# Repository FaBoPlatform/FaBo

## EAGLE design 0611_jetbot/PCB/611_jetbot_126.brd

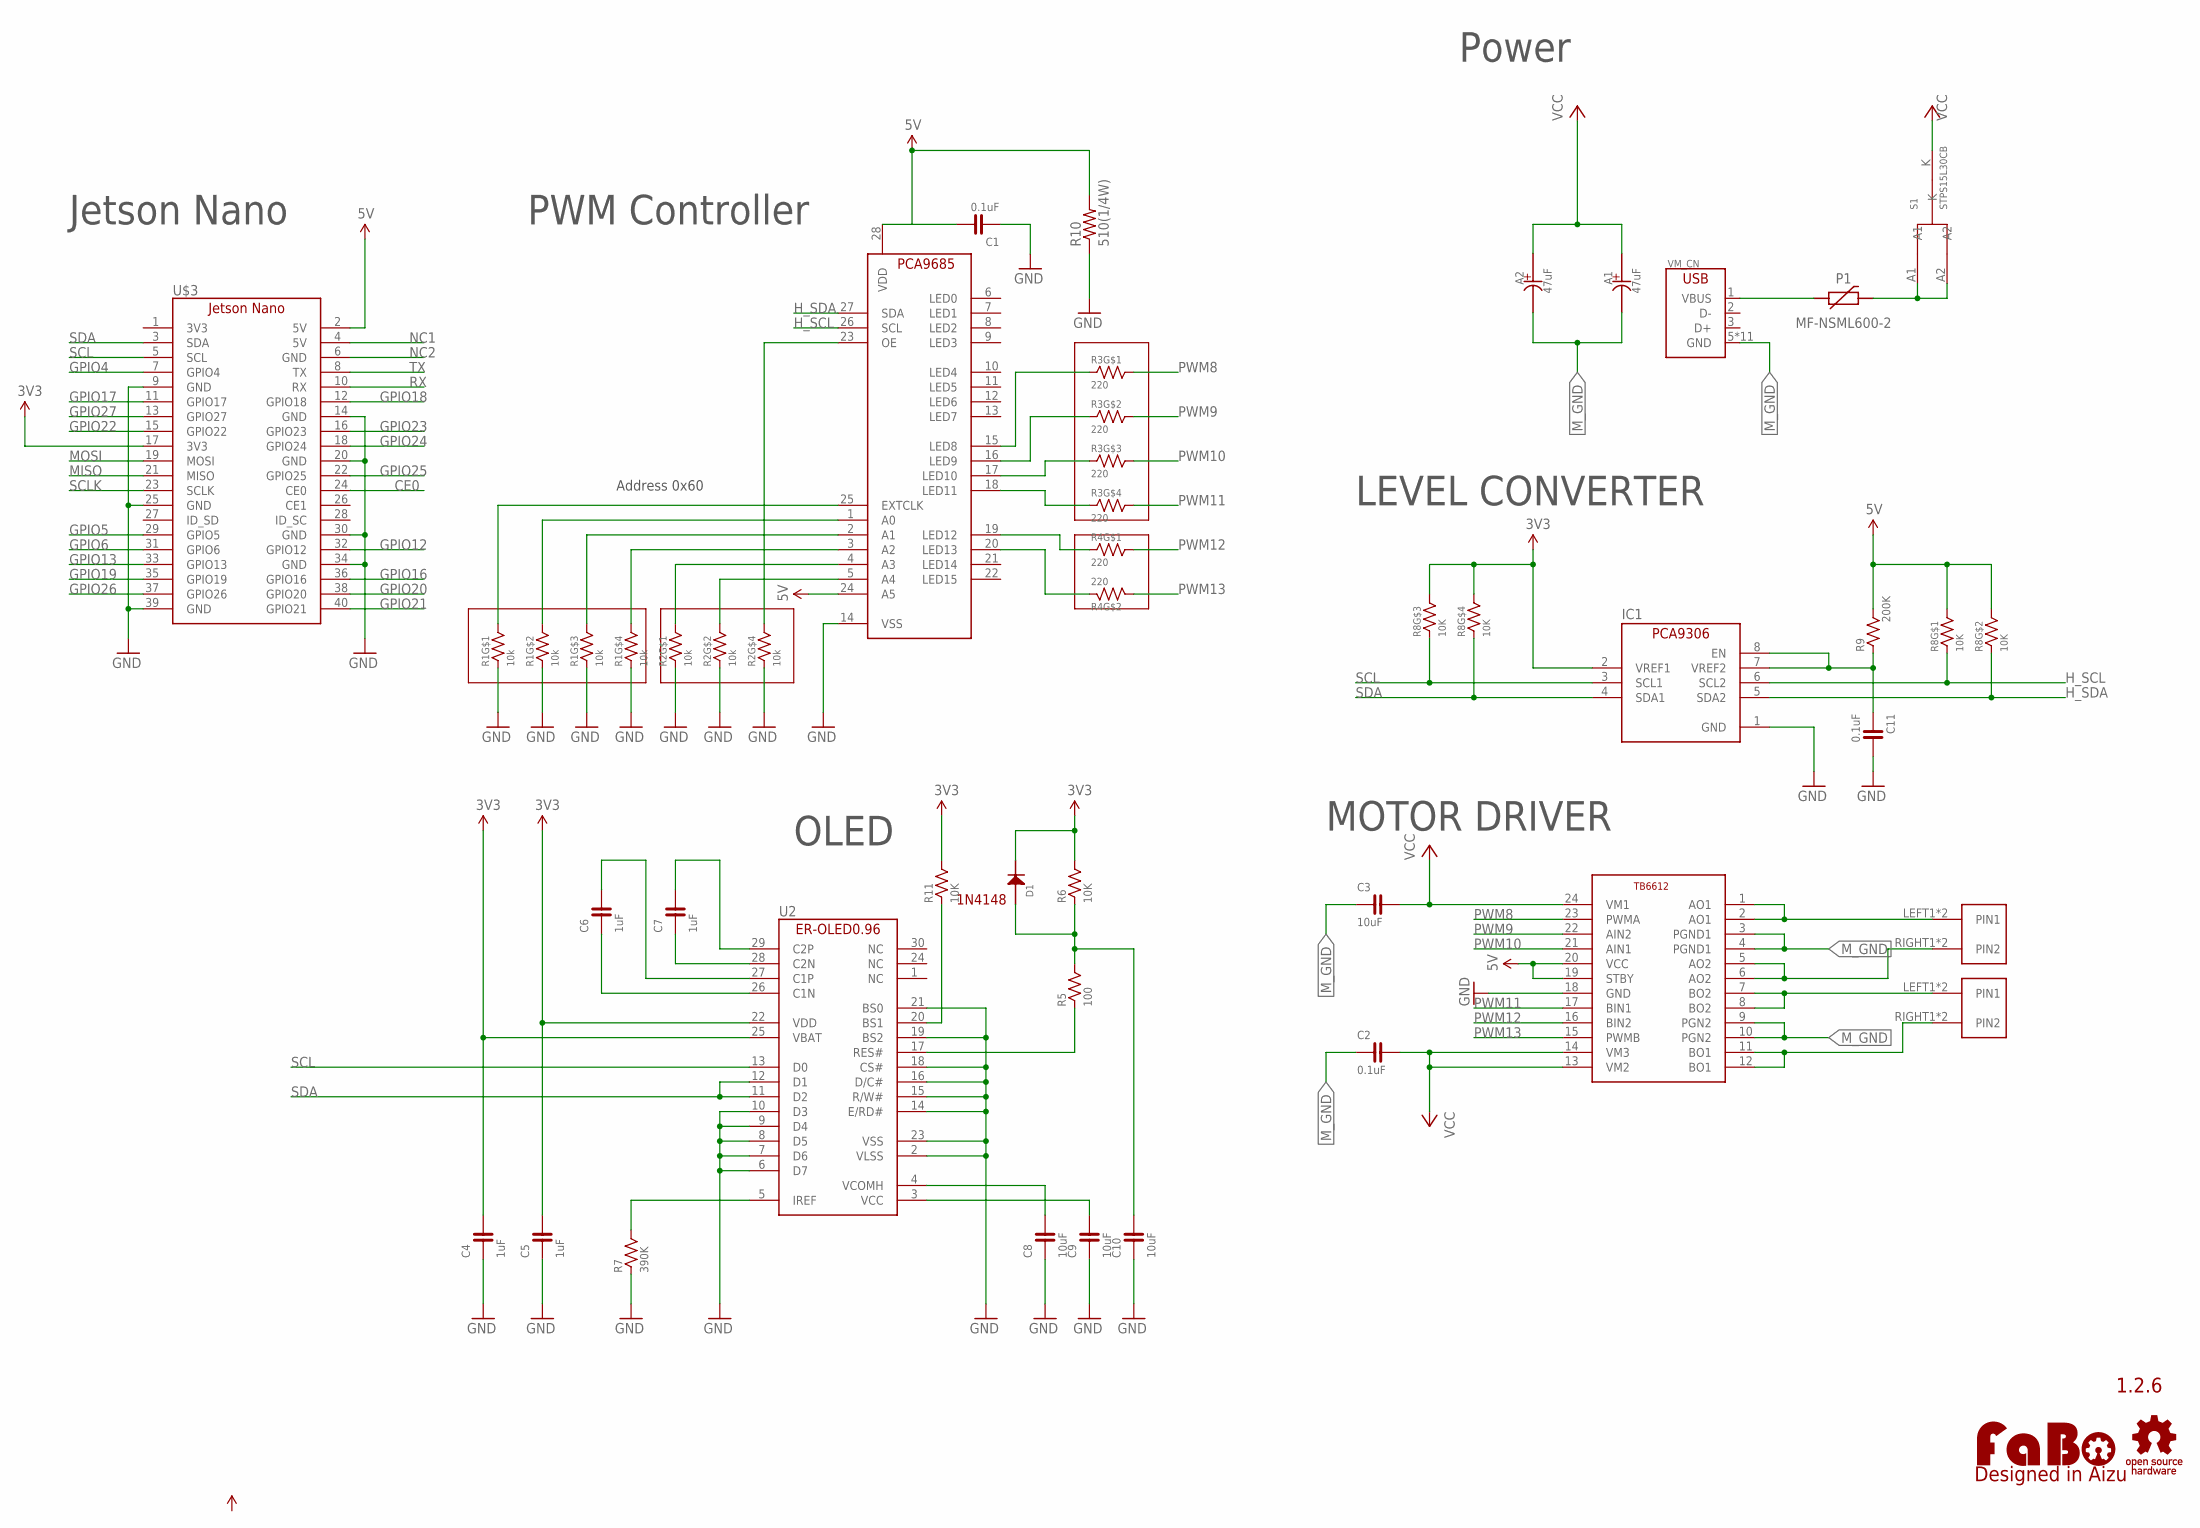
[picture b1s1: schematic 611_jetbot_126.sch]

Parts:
A1, A2: 47uF; D60
C1, C2, C11: 0.1uF; 0603
C3: 10uF; 0603
C4, C5, C6, C7: 1uF; 0603-BOTTOM
C8, C9, C10: 10uF; 0603-BOTTOM
D1: 1N4148; 1N4148W
IC1: PCA9306_SSOP; 8PIN-SSOP
LOGO1: LOGO_FABO-M; LOGO_FABO_M
P1: MF-NSML600-2; 1206
R1, R2: 10k; EXBV8V
R3, R4: 220; EXBV8V
R5: 100; 0603-BOTTOM
R6, R11: 10K; 0603-BOTTOM
R7: 390K; 0603-BOTTOM
R8: 10K; EXBV8V
R9: 200K; 0603
R10: 510(1/4W); R0805
S1: STPS15L30CB; STPS15L30C
U2: ER-OLED0.96-1ER-CON30HT-1_REV2; ER-CON30HT-1_REV2
U$3: JETSON_NANO
U$5: TB6612
U$6, U$8: ML-1400-S1
U$9: PCA9685
U$11: LOGO_OSHW-M_BOTTOM; LOGO_OSHW_M_BOTTOM
VM_CN: USB-ZX62D; ZX62D-B-5PA8

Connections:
3V3: C4.2, C5.2, D1.CATHODE, IC1.2 (VREF1), R6.2, R8.5 (2), R8.6 (2), R11.2, U2.22 (VDD), U2.25 (VBAT), U$3.17 (3V3)
5V: C1.2, R8.7 (2), R8.8 (2), R9.2, R10.2, U$3.2 (5V), U$5.19 (STBY), U$5.20 (VCC), U$9.24 (A5), U$9.28 (VDD)
CE0: U$3.24 (CE0)
GND: C1.1, C4.1, C5.1, C8.1, C9.1, C10.1, C11.2, IC1.1 (GND), R1.1, R1.2 (1), R1.3 (1), R1.4 (1), R2.1, R2.2 (1), R2.4 (1), R7.1, R10.1, U2.2 (VLSS), U2.6 (D7), U2.7 (D6), U2.8 (D5), U2.9 (D4), U2.10 (D3), U2.14 (E/RD#), U2.15 (R/W#), U2.16 (D/C#), U2.18 (CS#), U2.19 (BS2), U2.21 (BS0), U2.23 (VSS), U$3.9 (GND), U$3.14 (GND), U$3.20 (GND), U$3.25 (GND), U$3.30 (GND), U$3.34 (GND), U$3.39 (GND), U$5.18 (GND), U$9.14 (VSS)
GPIO4: U$3.7 (GPIO4)
GPIO5: U$3.29 (GPIO5)
GPIO6: U$3.31 (GPIO6)
GPIO12: U$3.32 (GPIO12)
GPIO13: U$3.33 (GPIO13)
GPIO16: U$3.36 (GPIO16)
GPIO17: U$3.11 (GPIO17)
GPIO18: U$3.12 (GPIO18)
GPIO19: U$3.35 (GPIO19)
GPIO20: U$3.38 (GPIO20)
GPIO21: U$3.40 (GPIO21)
GPIO22: U$3.15 (GPIO22)
GPIO23: U$3.16 (GPIO23)
GPIO24: U$3.18 (GPIO24)
GPIO25: U$3.22 (GPIO25)
GPIO26: U$3.37 (GPIO26)
GPIO27: U$3.13 (GPIO27)
H_SCL: IC1.6 (SCL2), R8.1, U$9.26 (SCL)
H_SDA: IC1.5 (SDA2), R8.2 (1), U$9.27 (SDA)
MISO: U$3.21 (MISO)
MOSI: U$3.19 (MOSI)
M_GND: A1.MINUS (-), A2.MINUS (-), C2.1, C3.1, U$5.3 (PGND1), U$5.4 (PGND1), U$5.9 (PGN2), U$5.10 (PGN2), VM_CN.5 (GND), VM_CN.B1 (GND), VM_CN.B2 (GND), VM_CN.B3 (GND), VM_CN.B4 (GND), VM_CN.T1 (GND), VM_CN.T2 (GND), VM_CN.T3 (GND), VM_CN.T4 (GND), VM_CN.T5 (GND), VM_CN.T6 (GND)
unnamed: R3.4 (1), U$9.18 (LED11)
unnamed: R3.3 (1), U$9.17 (LED10)
unnamed: R3.2 (1), U$9.16 (LED9)
unnamed: R3.1, U$9.15 (LED8)
unnamed: R4.1, U$9.19 (LED12)
unnamed: R2.5 (2), U$9.23 (OE)
unnamed: R1.8 (2), U$9.25 (EXTCLK)
unnamed: R1.7 (2), U$9.1 (A0)
unnamed: R1.6 (2), U$9.2 (A1)
unnamed: R1.5 (2), U$9.3 (A2)
unnamed: R2.8 (2), U$9.4 (A3)
unnamed: R2.7 (2), U$9.5 (A4)
unnamed: C6.2, U2.27 (C1P)
unnamed: R4.2 (1), U$9.20 (LED13)
unnamed: C6.1, U2.26 (C1N)
unnamed: U$5.1 (AO1), U$5.2 (AO1), U$6.LEFT1 (PIN1), U$6.LEFT2 (PIN1)
unnamed: U$5.5 (AO2), U$5.6 (AO2), U$6.RIGHT1 (PIN2), U$6.RIGHT2 (PIN2)
unnamed: C7.1, U2.28 (C2N)
unnamed: U$5.7 (BO2), U$5.8 (BO2), U$8.LEFT1 (PIN1), U$8.LEFT2 (PIN1)
unnamed: C7.2, U2.29 (C2P)
unnamed: U$5.11 (BO1), U$5.12 (BO1), U$8.RIGHT1 (PIN2), U$8.RIGHT2 (PIN2)
unnamed: R7.2, U2.5 (IREF)
unnamed: C8.2, U2.4 (VCOMH)
unnamed: C9.2, U2.3 (VCC)
unnamed: R5.1, U2.17 (RES#)
unnamed: C10.2, D1.ANODE, R5.2, R6.1
unnamed: R11.1, U2.20 (BS1)
unnamed: C11.1, IC1.7 (VREF2), IC1.8 (EN), R9.1
NC1: U$3.4 (5V)
NC2: U$3.6 (GND)
PTCP1: P1.P$1 (1), VM_CN.1 (VBUS)
PTCP2: P1.P$2 (2), S1.A1, S1.A2
PWM8: R3.8 (2), U$5.23 (PWMA)
PWM9: R3.7 (2), U$5.22 (AIN2)
PWM10: R3.6 (2), U$5.21 (AIN1)
PWM11: R3.5 (2), U$5.17 (BIN1)
PWM12: R4.8 (2), U$5.16 (BIN2)
PWM13: R4.7 (2), U$5.15 (PWMB)
RX: U$3.10 (RX)
SCL: IC1.3 (SCL1), R8.3 (1), U2.13 (D0), U$3.5 (SCL)
SCLK: U$3.23 (SCLK)
SDA: IC1.4 (SDA1), R8.4 (1), U2.11 (D2), U2.12 (D1), U$3.3 (SDA)
TX: U$3.8 (TX)
VCC: A1.PLUS (+), A2.PLUS (+), C2.2, C3.2, S1.K, U$5.13 (VM2), U$5.14 (VM3), U$5.24 (VM1)

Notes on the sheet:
1.2.6
Jetson Nano
PWM Controller
Power
MOTOR DRIVER
Address 0x60
1N4148
LEVEL CONVERTER
OLED

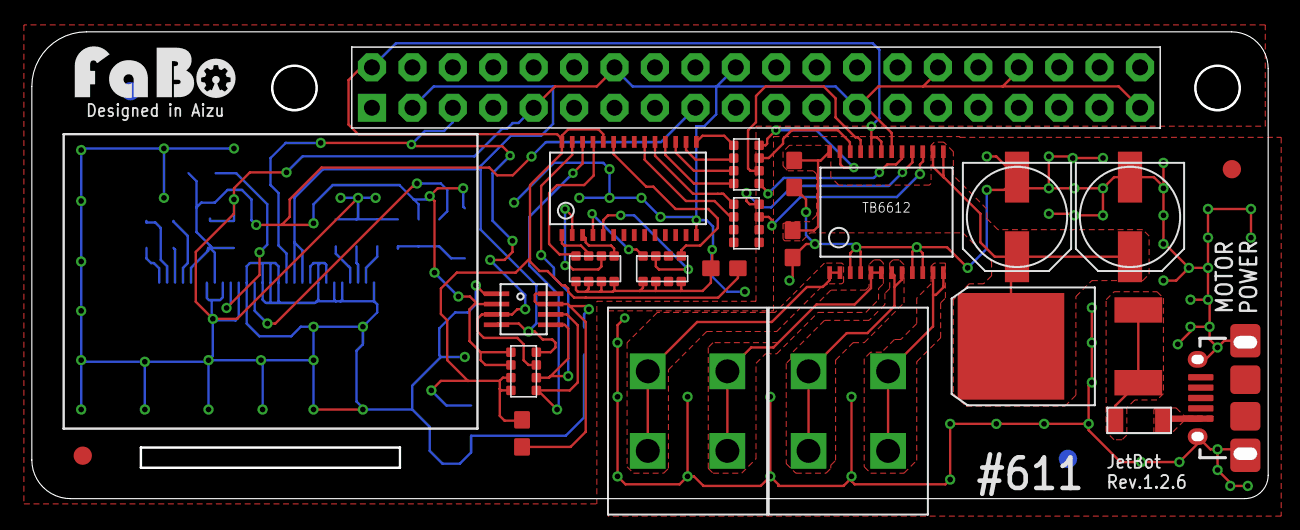
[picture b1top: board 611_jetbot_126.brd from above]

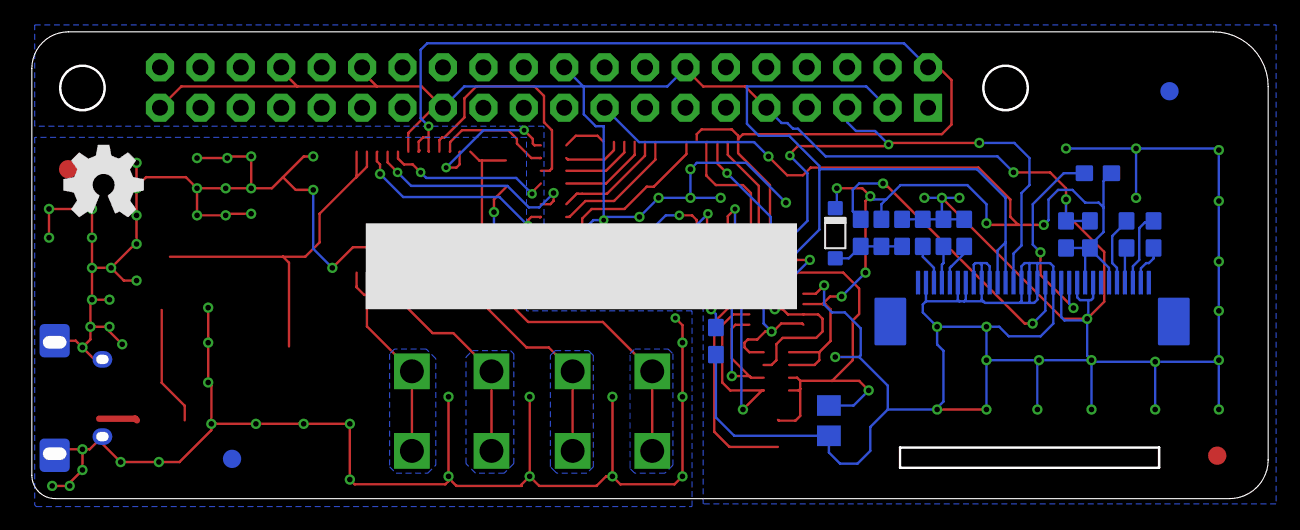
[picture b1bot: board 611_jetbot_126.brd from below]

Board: 2 copper layers, 77.7 x 29.3 mm, 41 parts (5 on the bottom side), 45 nets.

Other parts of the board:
U$2, U$4, U$7, U$10: MARK_POINT_3MM

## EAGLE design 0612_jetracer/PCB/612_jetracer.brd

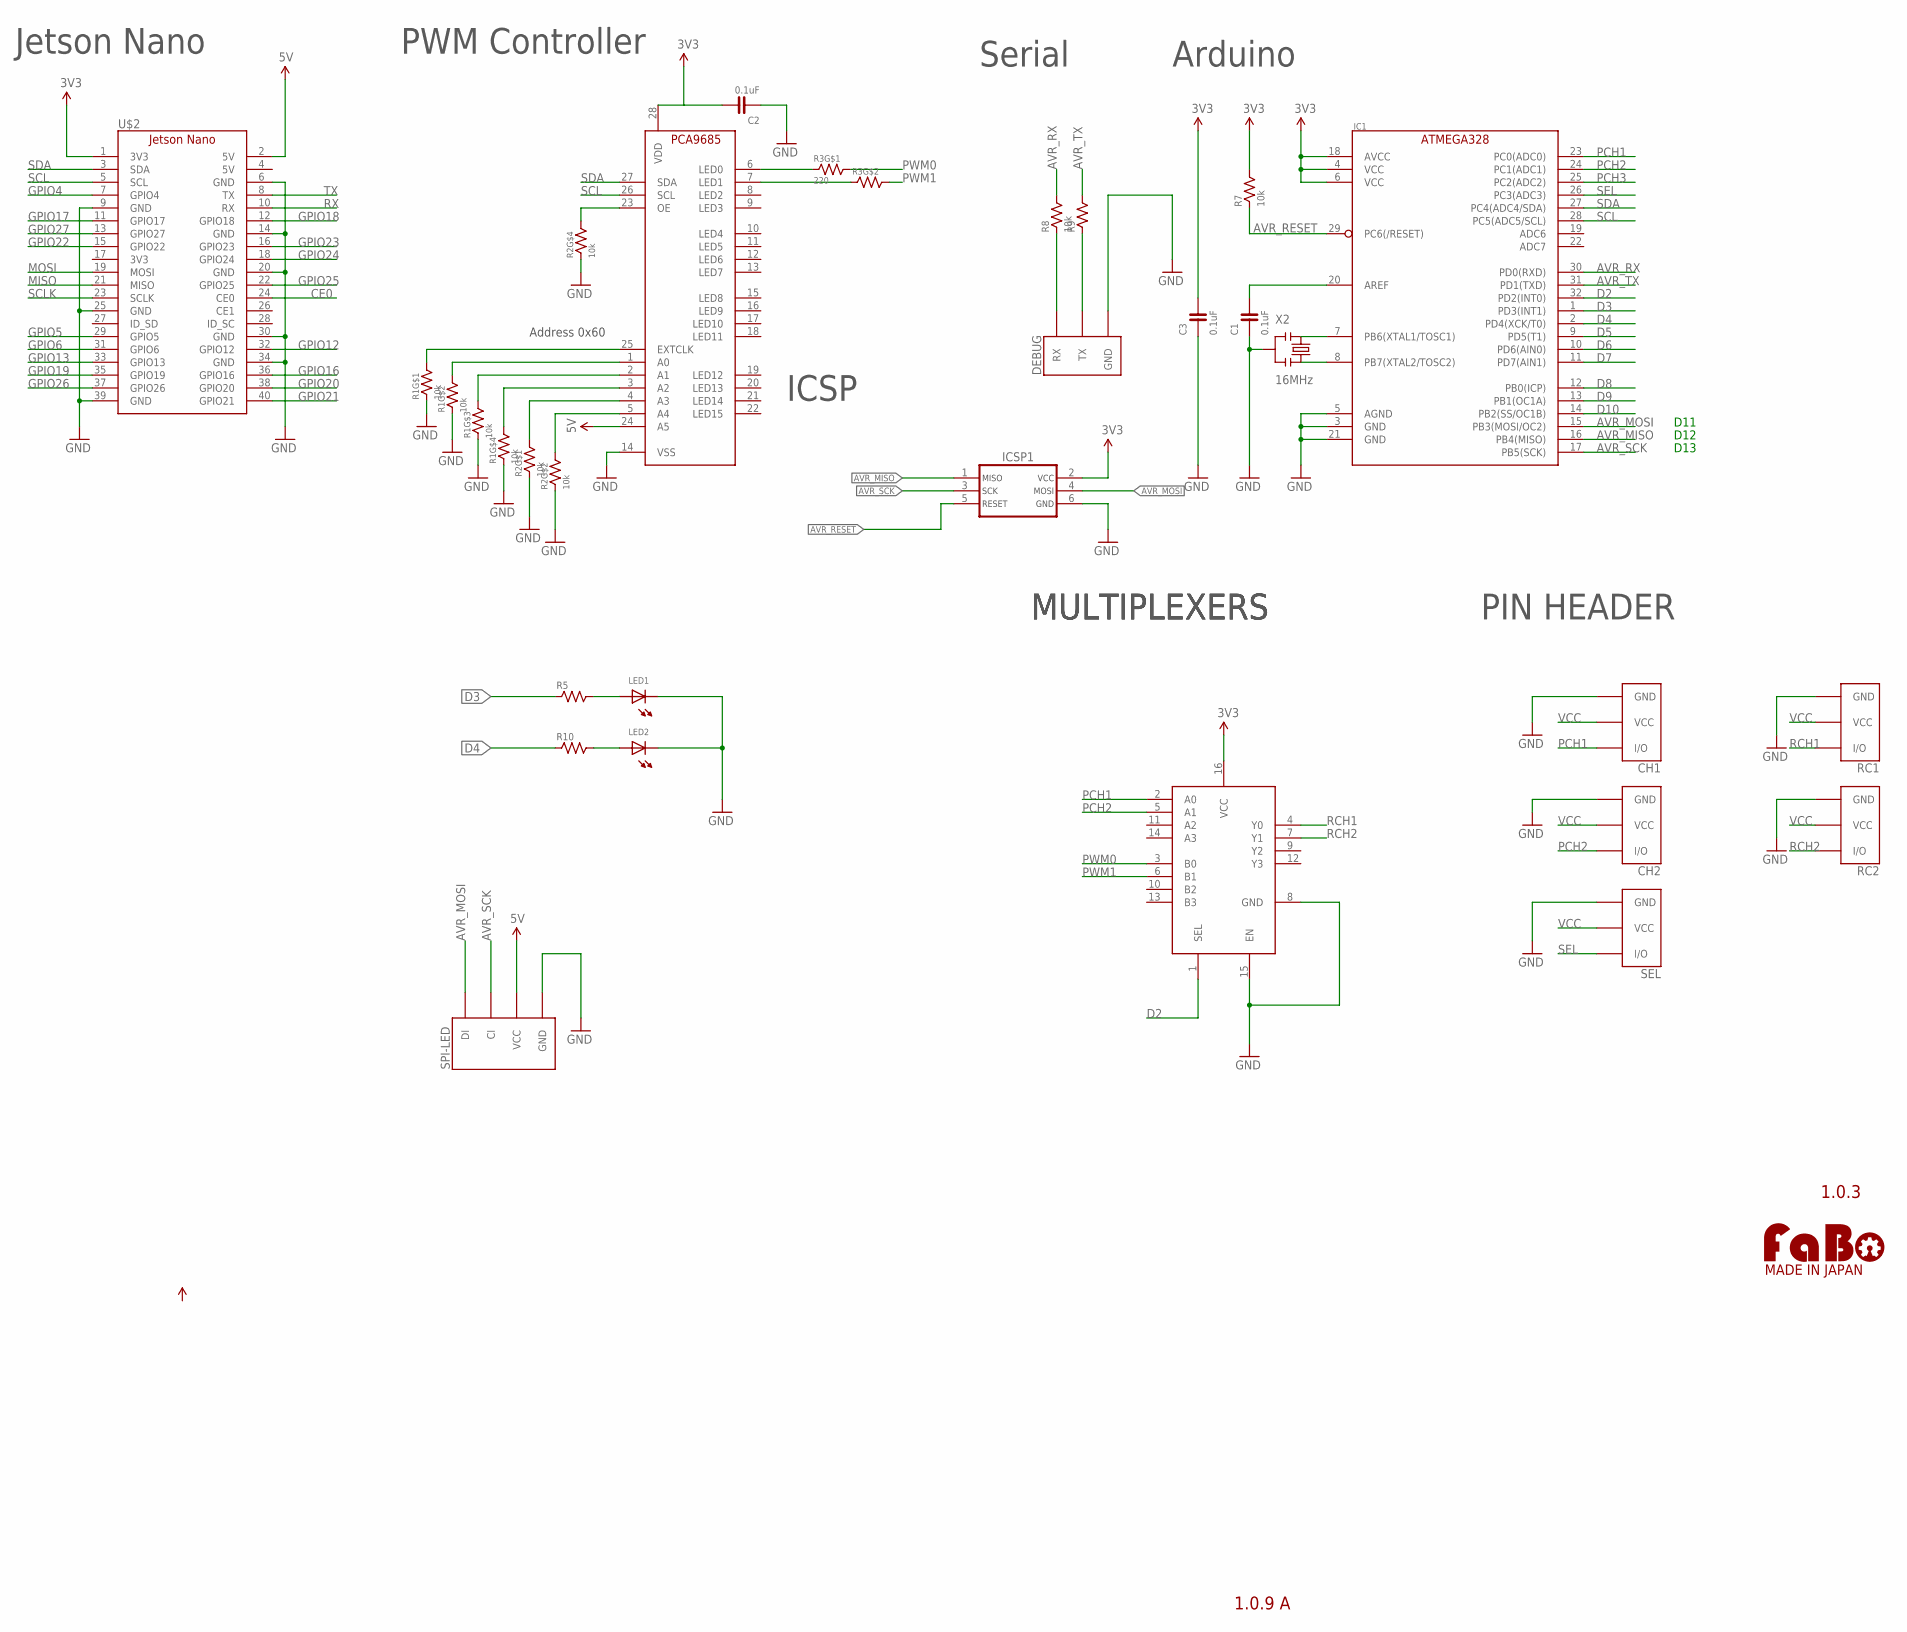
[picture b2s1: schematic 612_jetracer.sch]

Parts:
C1, C2, C3: 0.1uF; 0603
CH1, CH2: FABO_BRICK_3PIN-HEADER; FABO_BRICK_3PIN_HEADER
DEBUG: FABO_BRICK_3PIN_DEBUG
IC1: ATMEGA328P-AU; TQFP-32
IC3: MULTIPLEXERSMC74HC157A; TSSOP-16
ICSP1: ICSP_AVR-TC_NOHOLE; TC2030
LED1, LED2: LED-0603; 0603
R1, R2: 10k; EXBV8V
R3: 220; EXBV8V
R5, R7, R8, R9, R10: 10k; 0603
RC1, RC2: FABO_BRICK_3PIN-HEADER; FABO_BRICK_3PIN_HEADER
SEL: FABO_BRICK_3PIN-HEADER; FABO_BRICK_3PIN_HEADER
SPI-LED: FABO-SPI-LED-B04B; SPI-B04B-PASK-1
U$2: JETSON_NANO_NOBORDER; JETSON_NANO_NOBOARDER
U$9: PCA9685
U$14: LOGO_FABO-M; LOGO_FABO_MS
X2: 16MHz; CSTNE_V_C

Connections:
3V3: C2.2, C3.2, IC1.4 (VCC), IC1.6 (VCC), IC1.18 (AVCC), IC3.16 (VCC), ICSP1.2, R7.2, U$2.1 (3V3), U$9.28 (VDD)
5V: SPI-LED.VCC, U$2.2 (5V), U$9.24 (A5)
AVR_MISO: IC1.16 (PB4(MISO)), ICSP1.1
AVR_MOSI: IC1.15 (PB3(MOSI/OC2)), ICSP1.4, SPI-LED.DI
AVR_RESET: IC1.29 (PC6(/RESET)), ICSP1.5, R7.1
AVR_RX: IC1.30 (PD0(RXD)), R8.2
AVR_SCK: IC1.17 (PB5(SCK)), ICSP1.3, SPI-LED.CI
AVR_TX: IC1.31 (PD1(TXD)), R9.2
CE0: U$2.24 (CE0)
D2: IC1.32 (PD2(INT0)), IC3.1 (SEL)
D3: IC1.1 (PD3(INT1)), R5.1
D4: IC1.2 (PD4(XCK/T0)), R10.1
D5: IC1.9 (PD5(T1))
D6: IC1.10 (PD6(AIN0))
D7: IC1.11 (PD7(AIN1))
D8: IC1.12 (PB0(ICP))
D9: IC1.13 (PB1(OC1A))
D10: IC1.14 (PB2(SS/OC1B))
GND: C1.1, C2.1, C3.1, CH1.GND, CH2.GND, DEBUG.GND, IC1.3 (GND), IC1.5 (AGND), IC1.21 (GND), IC3.8 (GND), IC3.15 (EN), ICSP1.6, LED1.CATHODE, LED2.CATHODE, R1.1, R1.2 (1), R1.3 (1), R1.4 (1), R2.1, R2.2 (1), R2.4 (1), RC1.GND, RC2.GND, SEL.GND, SPI-LED.GND, U$2.6 (GND), U$2.9 (GND), U$2.14 (GND), U$2.20 (GND), U$2.25 (GND), U$2.30 (GND), U$2.34 (GND), U$2.39 (GND), U$9.14 (VSS), X2.2
GPIO4: U$2.7 (GPIO4)
GPIO5: U$2.29 (GPIO5)
GPIO6: U$2.31 (GPIO6)
GPIO12: U$2.32 (GPIO12)
GPIO13: U$2.33 (GPIO13)
GPIO16: U$2.36 (GPIO16)
GPIO17: U$2.11 (GPIO17)
GPIO18: U$2.12 (GPIO18)
GPIO19: U$2.35 (GPIO19)
GPIO20: U$2.38 (GPIO20)
GPIO21: U$2.40 (GPIO21)
GPIO22: U$2.15 (GPIO22)
GPIO23: U$2.16 (GPIO23)
GPIO24: U$2.18 (GPIO24)
GPIO25: U$2.22 (GPIO25)
GPIO26: U$2.37 (GPIO26)
GPIO27: U$2.13 (GPIO27)
MISO: U$2.21 (MISO)
MOSI: U$2.19 (MOSI)
unnamed: R3.1, U$9.6 (LED0)
unnamed: R3.2 (1), U$9.7 (LED1)
unnamed: C1.2, IC1.20 (AREF)
unnamed: IC1.8 (PB7(XTAL2/TOSC2)), X2.3
unnamed: DEBUG.RX, R8.1
unnamed: R2.5 (2), U$9.23 (OE)
unnamed: R1.8 (2), U$9.25 (EXTCLK)
unnamed: R1.7 (2), U$9.1 (A0)
unnamed: R1.6 (2), U$9.2 (A1)
unnamed: R1.5 (2), U$9.3 (A2)
unnamed: R2.8 (2), U$9.4 (A3)
unnamed: R2.7 (2), U$9.5 (A4)
unnamed: IC1.7 (PB6(XTAL1/TOSC1)), X2.1
unnamed: DEBUG.TX, R9.1
unnamed: LED1.ANODE, R5.2
unnamed: LED2.ANODE, R10.2
PCH1: CH1.I/O, IC1.23 (PC0(ADC0)), IC3.2 (A0)
PCH2: CH2.I/O, IC1.24 (PC1(ADC1)), IC3.5 (A1)
PCH3: IC1.25 (PC2(ADC2))
PWM0: IC3.3 (B0), R3.8 (2)
PWM1: IC3.6 (B1), R3.7 (2)
RCH1: IC3.4 (Y0), RC1.I/O
RCH2: IC3.7 (Y1), RC2.I/O
RX: U$2.10 (RX)
SCL: IC1.28 (PC5(ADC5/SCL)), U$2.5 (SCL), U$9.26 (SCL)
SCLK: U$2.23 (SCLK)
SDA: IC1.27 (PC4(ADC4/SDA)), U$2.3 (SDA), U$9.27 (SDA)
SEL: IC1.26 (PC3(ADC3)), SEL.I/O
TX: U$2.8 (TX)
VCC: CH1.VCC, CH2.VCC, RC1.VCC, RC2.VCC, SEL.VCC

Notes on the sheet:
1.0.3
Jetson Nano
PWM Controller
MULTIPLEXERS
Address 0x60
1.0.9 A
PIN HEADER
D11
D12
D13
Arduino
Serial
ICSP

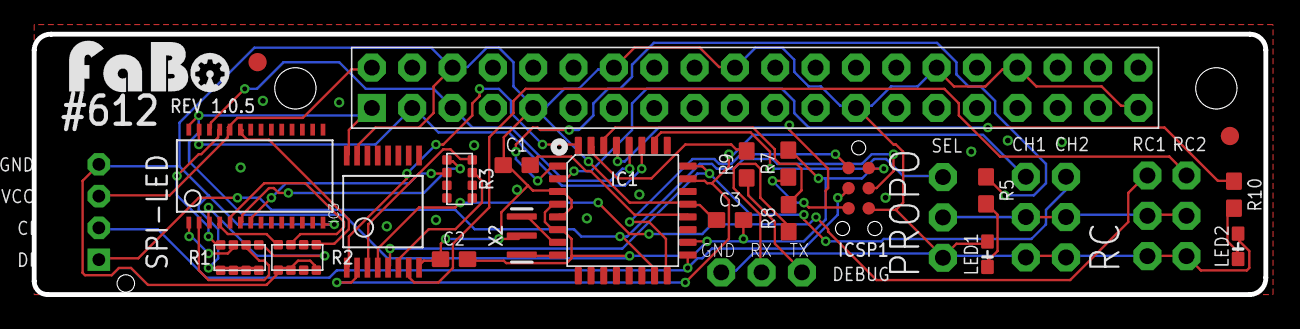
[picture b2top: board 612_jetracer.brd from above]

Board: 2 copper layers, 77.5 x 16.4 mm, 29 parts (0 on the bottom side), 38 nets.

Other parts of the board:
U$4, U$6: MARK_POINT_3MM

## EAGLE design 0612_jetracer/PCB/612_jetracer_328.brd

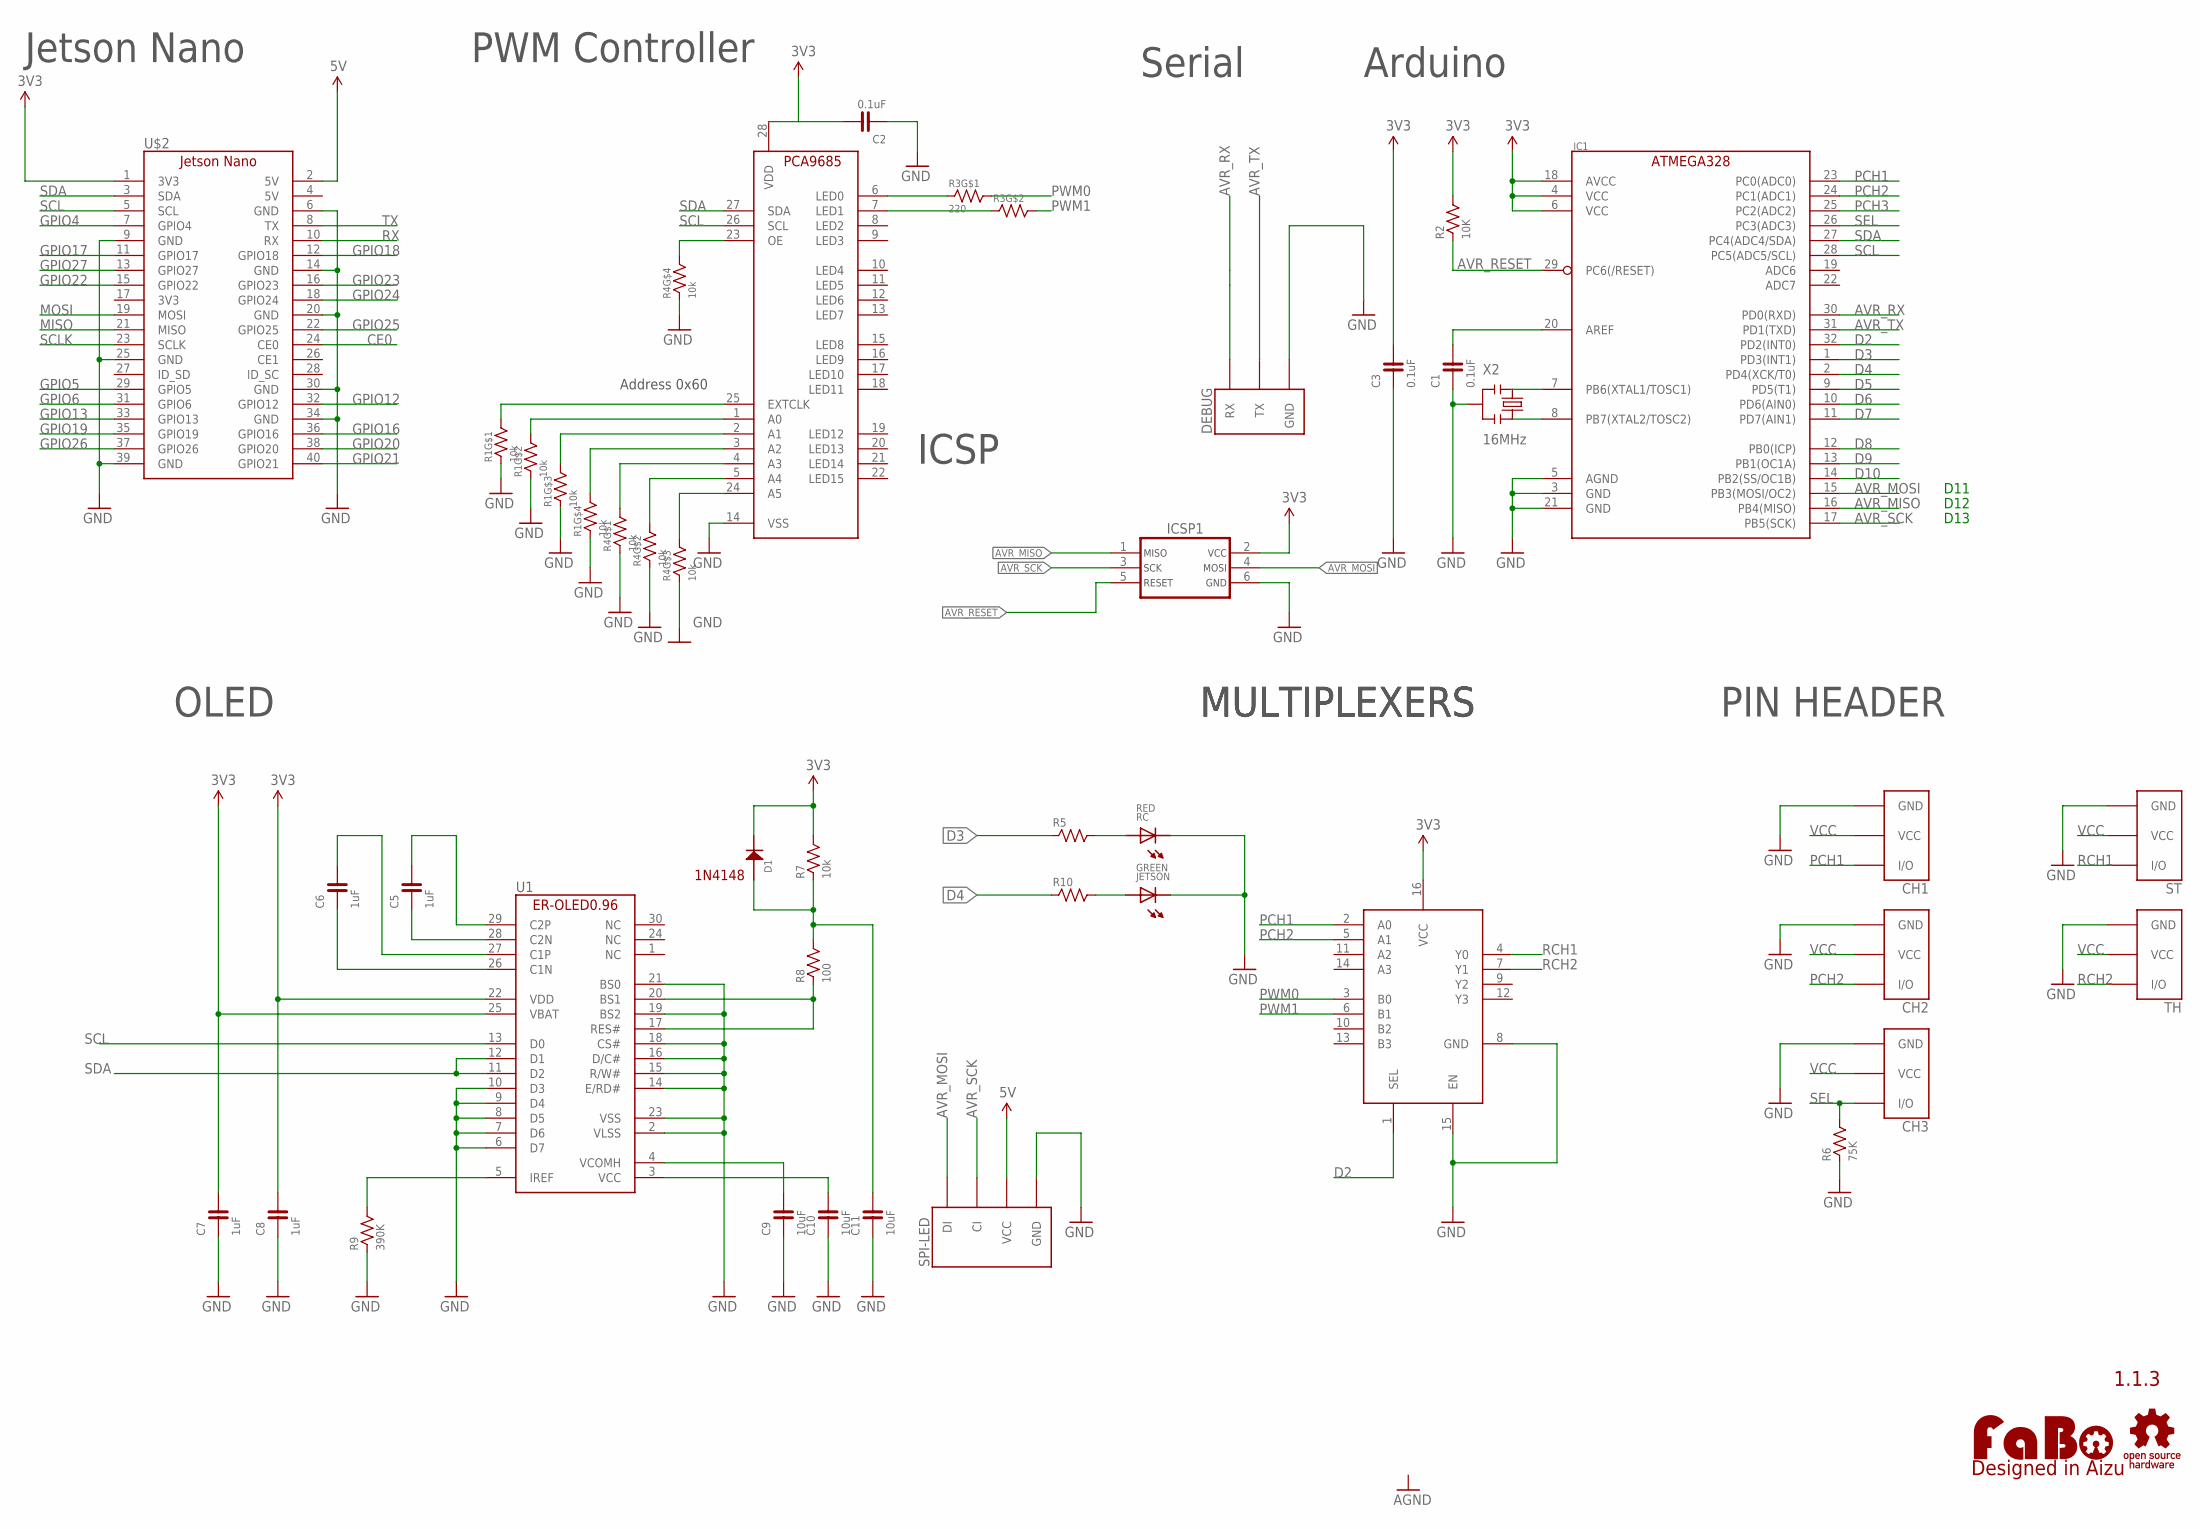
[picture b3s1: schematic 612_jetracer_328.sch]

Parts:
C1, C2, C3: 0.1uF; 0603
C5, C6, C7, C8: 1uF; 0603-BOTTOM
C9, C10, C11: 10uF; 0603-BOTTOM
CH1, CH2, CH3: FABO_BRICK_3PIN-HEADER; FABO_BRICK_3PIN_HEADER
D1: 1N4148; 1N4148W
DEBUG: FABO_BRICK_3PIN_DEBUG
IC1: ATMEGA328P-AU; TQFP-32
IC3: MULTIPLEXERSMC74HC157A; TSSOP-16
ICSP1: ICSP_AVR-TC_NOHOLE; TC2030
JETSON: GREEN; 0603
LOGO1: LOGO_FABO-S; LOGO_FABO_S
R1, R4: 10k; EXBV8V
R2: 10K; 0603
R3: 220; EXBV8V
R5, R10: 220; 0603
R6: 75K; 0603
R7: 10k; 0603-BOTTOM
R8: 100; 0603-BOTTOM
R9: 390K; 0603-BOTTOM
RC: RED; 0603
SPI-LED: FABO-SPI-LED-B04B; SPI-B04B-PASK-1
ST: FABO_BRICK_3PIN-HEADER; FABO_BRICK_3PIN_HEADER
TH: FABO_BRICK_3PIN-HEADER; FABO_BRICK_3PIN_HEADER
U1: ER-OLED0.96-1ER-CON30HT-1; ER-CON30HT-1
U$2: JETSON_NANO_NOBORDER; JETSON_NANO_NOBOARDER
U$3: PCA9685_BOTTOM
U$7: LOGO_OSHW-M_BOTTOM; LOGO_OSHW_M_BOTTOM
X2: 16MHz; CSTNE_V_C

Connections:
3V3: C2.2, C3.2, C7.2, D1.CATHODE, IC1.4 (VCC), IC1.6 (VCC), IC1.18 (AVCC), IC3.16 (VCC), ICSP1.2, R2.2, R7.2, U1.25 (VBAT), U$2.1 (3V3), U$3.28 (VDD)
5V: SPI-LED.VCC, U$2.2 (5V)
AVR_MISO: IC1.16 (PB4(MISO)), ICSP1.1
AVR_MOSI: IC1.15 (PB3(MOSI/OC2)), ICSP1.4, SPI-LED.DI
AVR_RESET: IC1.29 (PC6(/RESET)), ICSP1.5, R2.1
AVR_RX: DEBUG.RX, IC1.30 (PD0(RXD))
AVR_SCK: IC1.17 (PB5(SCK)), ICSP1.3, SPI-LED.CI
AVR_TX: DEBUG.TX, IC1.31 (PD1(TXD))
CE0: U$2.24 (CE0)
D2: IC1.32 (PD2(INT0)), IC3.1 (SEL)
D3: IC1.1 (PD3(INT1)), R5.1
D4: IC1.2 (PD4(XCK/T0)), R10.1
D5: IC1.9 (PD5(T1))
D6: IC1.10 (PD6(AIN0))
D7: IC1.11 (PD7(AIN1))
D8: IC1.12 (PB0(ICP))
D9: IC1.13 (PB1(OC1A))
D10: IC1.14 (PB2(SS/OC1B))
GND: C1.1, C2.1, C3.1, C7.1, C8.1, C9.1, C10.1, C11.1, CH1.GND, CH2.GND, CH3.GND, DEBUG.GND, IC1.3 (GND), IC1.5 (AGND), IC1.21 (GND), IC3.8 (GND), IC3.15 (EN), ICSP1.6, JETSON.CATHODE, R1.1, R1.2 (1), R1.3 (1), R1.4 (1), R4.1, R4.2 (1), R4.3 (1), R4.4 (1), R6.1, R9.1, RC.CATHODE, SPI-LED.GND, ST.GND, TH.GND, U1.2 (VLSS), U1.6 (D7), U1.7 (D6), U1.8 (D5), U1.9 (D4), U1.10 (D3), U1.14 (E/RD#), U1.15 (R/W#), U1.16 (D/C#), U1.18 (CS#), U1.19 (BS2), U1.21 (BS0), U1.23 (VSS), U$2.6 (GND), U$2.9 (GND), U$2.14 (GND), U$2.20 (GND), U$2.25 (GND), U$2.30 (GND), U$2.34 (GND), U$2.39 (GND), U$3.14 (VSS), X2.2
GPIO4: U$2.7 (GPIO4)
GPIO5: U$2.29 (GPIO5)
GPIO6: U$2.31 (GPIO6)
GPIO12: U$2.32 (GPIO12)
GPIO13: U$2.33 (GPIO13)
GPIO16: U$2.36 (GPIO16)
GPIO17: U$2.11 (GPIO17)
GPIO18: U$2.12 (GPIO18)
GPIO19: U$2.35 (GPIO19)
GPIO20: U$2.38 (GPIO20)
GPIO21: U$2.40 (GPIO21)
GPIO22: U$2.15 (GPIO22)
GPIO23: U$2.16 (GPIO23)
GPIO24: U$2.18 (GPIO24)
GPIO25: U$2.22 (GPIO25)
GPIO26: U$2.37 (GPIO26)
GPIO27: U$2.13 (GPIO27)
MISO: U$2.21 (MISO)
MOSI: U$2.19 (MOSI)
unnamed: R3.1, U$3.6 (LED0)
unnamed: R3.2 (1), U$3.7 (LED1)
unnamed: C1.2, IC1.20 (AREF)
unnamed: IC1.8 (PB7(XTAL2/TOSC2)), X2.3
unnamed: R4.5 (2), U$3.23 (OE)
unnamed: R1.8 (2), U$3.25 (EXTCLK)
unnamed: R1.7 (2), U$3.1 (A0)
unnamed: R1.6 (2), U$3.2 (A1)
unnamed: R1.5 (2), U$3.3 (A2)
unnamed: R4.8 (2), U$3.4 (A3)
unnamed: R4.7 (2), U$3.5 (A4)
unnamed: R4.6 (2), U$3.24 (A5)
unnamed: IC1.7 (PB6(XTAL1/TOSC1)), X2.1
unnamed: C6.2, U1.27 (C1P)
unnamed: R5.2, RC.ANODE
unnamed: JETSON.ANODE, R10.2
unnamed: C6.1, U1.26 (C1N)
unnamed: C5.1, U1.28 (C2N)
unnamed: C5.2, U1.29 (C2P)
unnamed: R9.2, U1.5 (IREF)
unnamed: C9.2, U1.4 (VCOMH)
unnamed: C10.2, U1.3 (VCC)
unnamed: R8.1, U1.17 (RES#), U1.20 (BS1)
unnamed: C11.2, D1.ANODE, R7.1, R8.2
unnamed: C8.2, U1.22 (VDD)
PCH1: CH1.I/O, IC1.23 (PC0(ADC0)), IC3.2 (A0)
PCH2: CH2.I/O, IC1.24 (PC1(ADC1)), IC3.5 (A1)
PCH3: IC1.25 (PC2(ADC2))
PWM0: IC3.3 (B0), R3.8 (2)
PWM1: IC3.6 (B1), R3.7 (2)
RCH1: IC3.4 (Y0), ST.I/O
RCH2: IC3.7 (Y1), TH.I/O
RX: U$2.10 (RX)
SCL: IC1.28 (PC5(ADC5/SCL)), U1.13 (D0), U$2.5 (SCL), U$3.26 (SCL)
SCLK: U$2.23 (SCLK)
SDA: IC1.27 (PC4(ADC4/SDA)), U1.11 (D2), U1.12 (D1), U$2.3 (SDA), U$3.27 (SDA)
SEL: CH3.I/O, IC1.26 (PC3(ADC3)), R6.2
TX: U$2.8 (TX)
VCC: CH1.VCC, CH2.VCC, CH3.VCC, ST.VCC, TH.VCC

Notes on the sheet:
1.1.3
Jetson Nano
PWM Controller
MULTIPLEXERS
Address 0x60
PIN HEADER
D11
D12
D13
Arduino
Serial
ICSP
1N4148
OLED

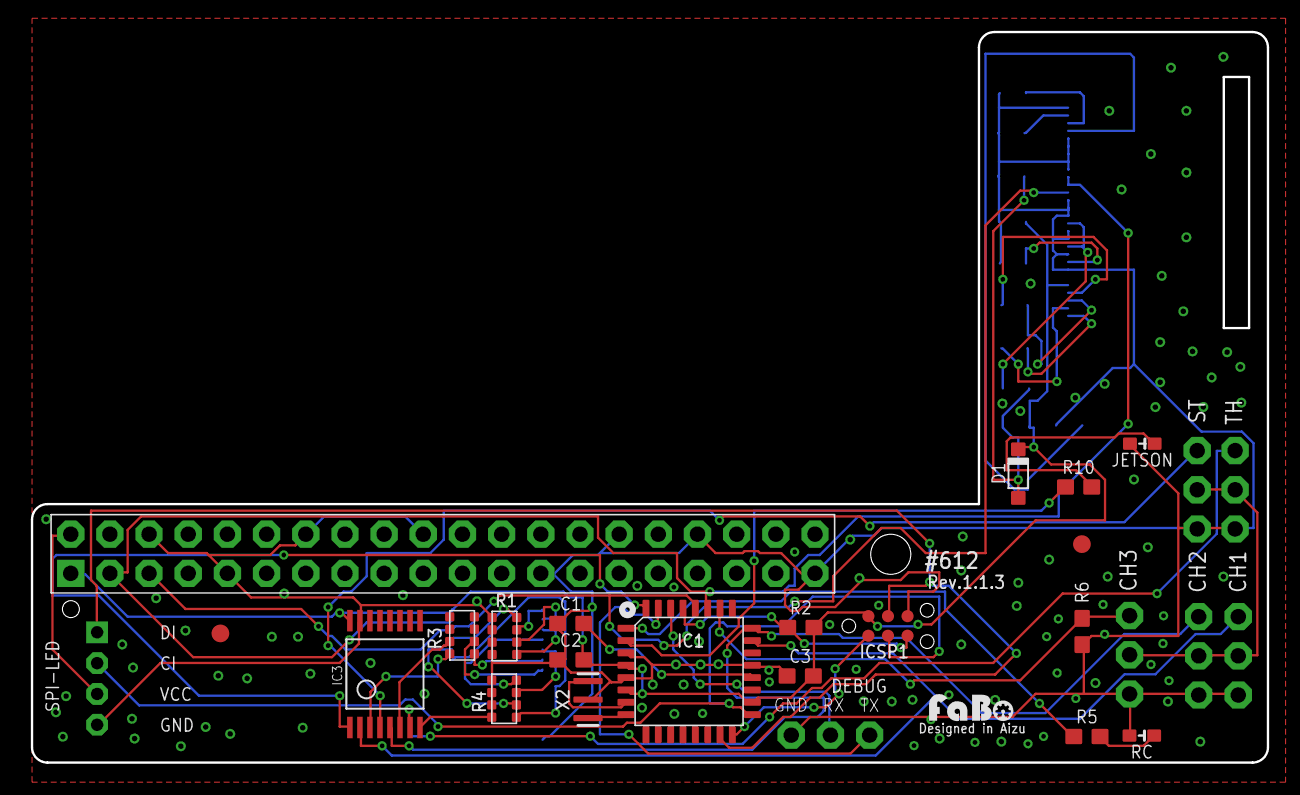
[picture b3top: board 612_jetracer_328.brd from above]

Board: 2 copper layers, 80.1 x 47.4 mm, 41 parts (0 on the bottom side), 47 nets.

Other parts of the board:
U$4, U$6: MARK_POINT_3MM

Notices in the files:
parts and their libraries:
FaBo-etc: Released under the Creative Commons Attribution-ShareAlike 4.0 License
https://creativecommons.org/licenses/by-sa/4.0
FaBo-etc: Released under the Creative Commons
